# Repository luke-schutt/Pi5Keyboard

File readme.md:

# Pi5 Keyboard

A monoblock split 38-key keyboard inspired by the [ChocV](https://github.com/brickbots/chocV).

## Design

The keyboard consists of two boards, the main PCB and a mounting plate, and and optional MCU cover. The switches are on a 19x19mm grid with the footprint supporting Kailh Choc V1, V2, Gateron low profile, and MX switches.

The bottom of the board features footprints for a convenient reset switch and a JST connector with 3.3v and I2C data that (again, untested) should support [Qwiic](https://www.sparkfun.com/qwiic) or [STEMMA QT](https://learn.adafruit.com/introducing-adafruit-stemma-qt/what-is-stemma-qt) accessories.

The spacing between the PCB and plate with V2 Choc switches doesn't allow for SMD parts. Fortunately the diode footprint also allows though-hole components so they can be soldered under the PCB.

## Build one!

Check out the [gerbers folder](Gerbers/) for zip files that can be uploaded to your PCB manufacturer of your choice.

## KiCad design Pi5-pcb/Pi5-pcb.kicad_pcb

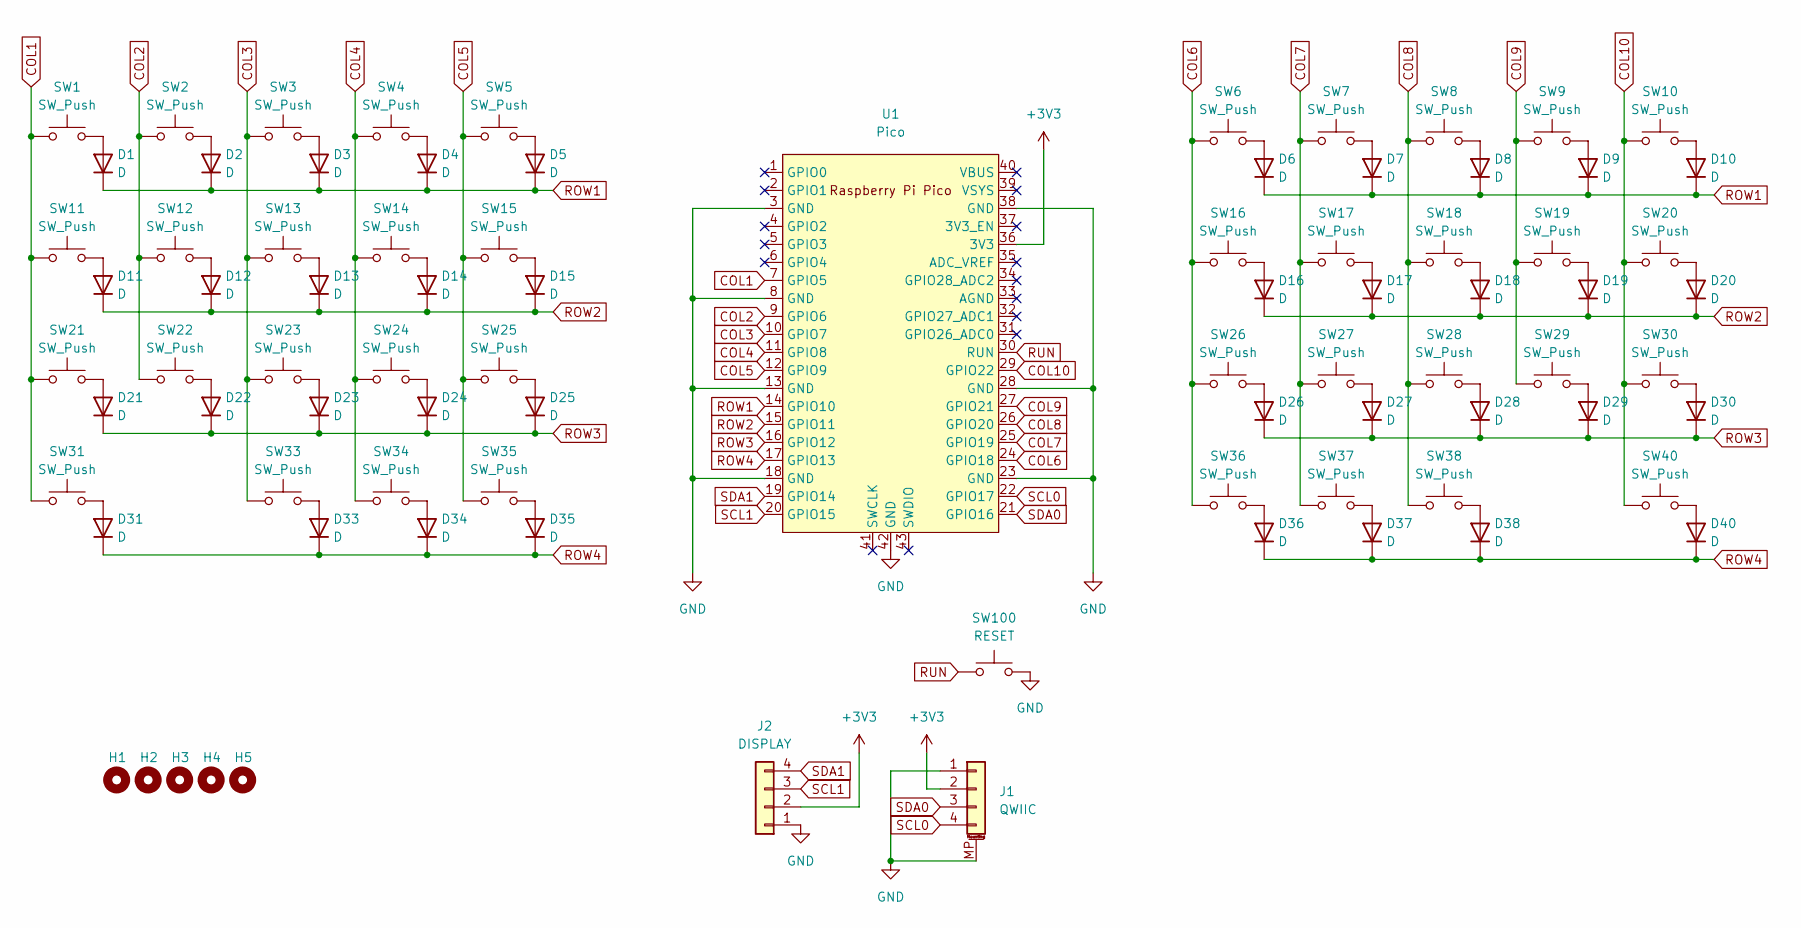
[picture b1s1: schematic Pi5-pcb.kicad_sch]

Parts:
D1, D2, D3, D4, D5, D6, D7, D8, D9, D10, D11, D12, D13, D14, D15, D16, D17, D18, D19, D20, D21, D22, D23, D24, D25, D26, D27, D28, D29, D30, D31, D33, D34, D35, D36, D37, D38, D40: D; Multi-diode
H1, H2, H3, H4: MountingHole_Pad; MountingHole_2.2mm_M2
H5: MountingHole_Pad; PiPico-Mounting
J1: QWIIC; JST_SH_SM04B-SRSS-TB_1x04-1MP_P1.00mm_Horizontal
J2: DISPLAY; PinHeader_1x04_P2.54mm_Vertical
SW1, SW2, SW3, SW4, SW5, SW6, SW7, SW8, SW9, SW10, SW11, SW12, SW13, SW14, SW15, SW16, SW17, SW18, SW19, SW20, SW21, SW22, SW23, SW24, SW25, SW26, SW27, SW28, SW29, SW30, SW31, SW33, SW34, SW35, SW36, SW37, SW38, SW40: SW_Push; Low Profile GC plus MX
SW100: RESET; Tact Switch (PTS815)
U1: Pico; PiPico

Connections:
+3V3: J1.2, J2.2, U1.36 (3V3)
COL1: SW1.1, SW11.1, SW21.1, SW31.1, U1.7 (GPIO5)
COL2: SW2.1, SW12.1, SW22.1, U1.9 (GPIO6)
COL3: SW3.1, SW13.1, SW23.1, SW33.1, U1.10 (GPIO7)
COL4: SW4.1, SW14.1, SW24.1, SW34.1, U1.11 (GPIO8)
COL5: SW5.1, SW15.1, SW25.1, SW35.1, U1.12 (GPIO9)
COL6: SW6.1, SW16.1, SW26.1, SW36.1, U1.24 (GPIO18)
COL7: SW7.1, SW17.1, SW27.1, SW37.1, U1.25 (GPIO19)
COL8: SW8.1, SW18.1, SW28.1, SW38.1, U1.26 (GPIO20)
COL9: SW9.1, SW19.1, SW29.1, U1.27 (GPIO21)
COL10: SW10.1, SW20.1, SW30.1, SW40.1, U1.29 (GPIO22)
GND: J1.1, J1.MP (MountPin), J2.1, SW100.2, U1.3 (GND), U1.8 (GND), U1.13 (GND), U1.18 (GND), U1.23 (GND), U1.28 (GND), U1.38 (GND), U1.42 (GND)
unnamed: D1.2 (A), SW1.2
unnamed: D2.2 (A), SW2.2
unnamed: D3.2 (A), SW3.2
unnamed: D4.2 (A), SW4.2
unnamed: D5.2 (A), SW5.2
unnamed: D6.2 (A), SW6.2
unnamed: D7.2 (A), SW7.2
unnamed: D8.2 (A), SW8.2
unnamed: D9.2 (A), SW9.2
unnamed: D10.2 (A), SW10.2
unnamed: D11.2 (A), SW11.2
unnamed: D12.2 (A), SW12.2
unnamed: D13.2 (A), SW13.2
unnamed: D14.2 (A), SW14.2
unnamed: D15.2 (A), SW15.2
unnamed: D16.2 (A), SW16.2
unnamed: D17.2 (A), SW17.2
unnamed: D18.2 (A), SW18.2
unnamed: D19.2 (A), SW19.2
unnamed: D20.2 (A), SW20.2
unnamed: D21.2 (A), SW21.2
unnamed: D22.2 (A), SW22.2
unnamed: D23.2 (A), SW23.2
unnamed: D24.2 (A), SW24.2
unnamed: D25.2 (A), SW25.2
unnamed: D26.2 (A), SW26.2
unnamed: D27.2 (A), SW27.2
unnamed: D28.2 (A), SW28.2
unnamed: D29.2 (A), SW29.2
unnamed: D30.2 (A), SW30.2
unnamed: D31.2 (A), SW31.2
unnamed: D33.2 (A), SW33.2
unnamed: D34.2 (A), SW34.2
unnamed: D35.2 (A), SW35.2
unnamed: D36.2 (A), SW36.2
unnamed: D37.2 (A), SW37.2
unnamed: D38.2 (A), SW38.2
unnamed: D40.2 (A), SW40.2
ROW1: D1.1 (K), D2.1 (K), D3.1 (K), D4.1 (K), D5.1 (K), D6.1 (K), D7.1 (K), D8.1 (K), D9.1 (K), D10.1 (K), U1.14 (GPIO10)
ROW2: D11.1 (K), D12.1 (K), D13.1 (K), D14.1 (K), D15.1 (K), D16.1 (K), D17.1 (K), D18.1 (K), D19.1 (K), D20.1 (K), U1.15 (GPIO11)
ROW3: D21.1 (K), D22.1 (K), D23.1 (K), D24.1 (K), D25.1 (K), D26.1 (K), D27.1 (K), D28.1 (K), D29.1 (K), D30.1 (K), U1.16 (GPIO12)
ROW4: D31.1 (K), D33.1 (K), D34.1 (K), D35.1 (K), D36.1 (K), D37.1 (K), D38.1 (K), D40.1 (K), U1.17 (GPIO13)
RUN: SW100.1, U1.30 (RUN)
SCL0: J1.4, U1.22 (GPIO17)
SCL1: J2.3, U1.20 (GPIO15)
SDA0: J1.3, U1.21 (GPIO16)
SDA1: J2.4, U1.19 (GPIO14)

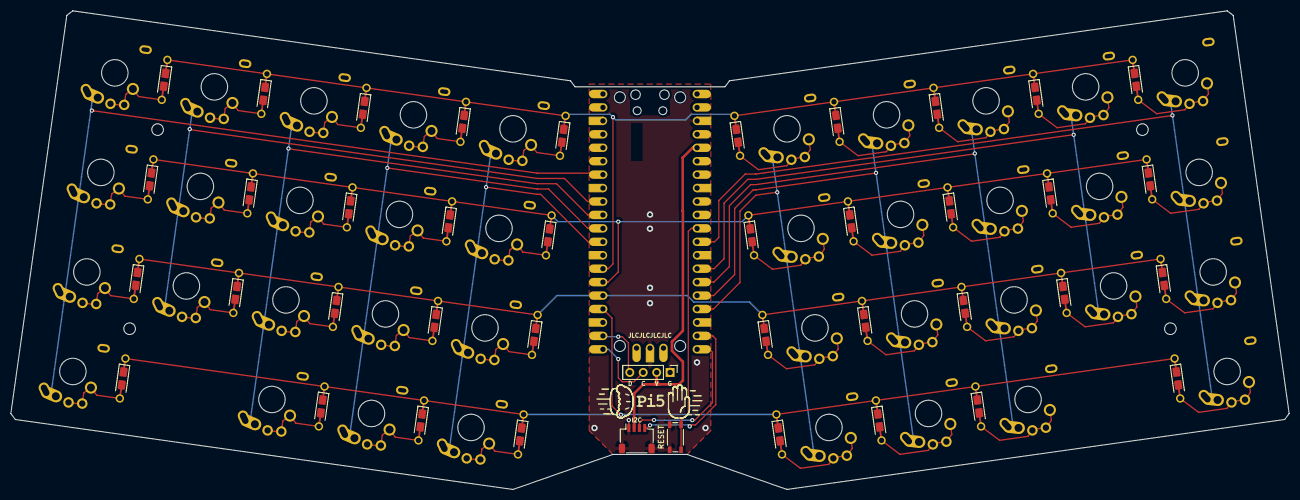
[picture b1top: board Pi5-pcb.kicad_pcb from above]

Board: 2 copper layers, 241.6 x 90.5 mm, 85 parts (0 on the bottom side), 59 nets.

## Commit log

2022-11-25 Initial commit.
2022-11-25 Pi5 Keyboard revision 1.
2022-11-30 Added controller cover to plate project including a retroactive rev0 design.
2022-12-16 Moved custom footprints into Pi5 footprint library.
2023-01-27 Documentation and keymap art update.
2023-02-13 Documentation updates.
2023-02-13 Updated `.gitignore` for folder with untracked experiments.
2023-02-26 Added OpenSCAD case design.
